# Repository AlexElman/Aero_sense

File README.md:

# Aero_sense
Can-Sat 2026/27 project group 2 from HTL Rennweg

## Core

| Component | Manufacturer / Part Number | Description |
|-----------|---------------------------|-------------|
| **MCU** | STMicroelectronics **STM32F415ZGT6** | High-performance ARM Cortex-M4 microcontroller (168 MHz, 1 MB Flash, 192 KB RAM). Selected for processing power, multiple peripherals (SPI, I²C, UART), and suitability for real-time sensor fusion and telemetry. |

## Sensors

| Component | Manufacturer / Part Number | Description |
|-----------|---------------------------|-------------|
| **Barometer** | Bosch **BMP581** | High-accuracy, low-noise absolute pressure sensor. Excellent for precise altitude determination. Digital SPI/I²C interface. Preferred over BMP390 for better noise performance and resolution. |
| **IMU** | TDK InvenSense **ICM-42688-P** | High-performance 6-axis IMU (3-axis gyroscope + 3-axis accelerometer). Low noise, high stability, SPI interface. Chosen for accurate attitude and motion sensing during flight. |
| **GNSS** | u-blox **SAM-M10Q** | Compact concurrent multi-GNSS module (GPS, GLONASS, Galileo, BeiDou). Good sensitivity and update rate for position/velocity tracking. UART interface. |
| **Temperature & Humidity** | Sensirion **SHT45** | High-accuracy digital temperature and relative humidity sensor. Excellent long-term stability and low power consumption. I²C interface. |
| **VOC / Air Quality** | Sensirion **SGP41** | Digital VOC + NOx sensor providing VOC Index and NOx Index outputs. Significantly better long-term stability and lower power than BME688. I²C interface. |

## Communication

| Component | Manufacturer / Part Number | Description |
|-----------|---------------------------|-------------|
| **LoRa Telemetry** | MicoAir **LR868F** (with 2 dBi antenna) | 868 MHz LoRa telemetry radio (500 mW). Long-range, interference-resistant link for real-time data downlink. UART interface. Suitable for CanSat telemetry ranges. |

## Power

| Component | Manufacturer / Part Number | Description |
|-----------|---------------------------|-------------|
| **Battery** | Molicel **INR-21700-P50B** (P50B) | Single high-power 21700 Li-ion cell (nominal 3.6 V, 5000 mAh, up to 60 A continuous). Excellent energy and power density for the limited volume of a CanSat. |
| **Battery Charger / PMIC** | Texas Instruments **BQ25895** | Highly integrated battery charge management IC with system power path management. Supports fast charging of the P50B cell and provides regulated system power. |

## Board-to-Board Interconnect

| Component | Manufacturer / Part Number | Description |
|-----------|---------------------------|-------------|
| **Mezzanine Connectors** | Amphenol **BergStak 0.40 mm** (2×) | Two board-to-board stacking connectors (recommended 20-pin version with 4.0 mm stack height). Provides power, SPI, I²C, UART and multiple GND connections between the three circular PCBs while offering good mechanical rigidity and vibration resistance. |

## Mechanical / PCB Notes

- Three custom semi-circular PCBs ( ≈58 mm diameter)
- Sensors requiring fresh air (BMP581, SHT45, SGP41) placed on the bottom board with controlled side vents
- Charging and data-transfer via USB-C

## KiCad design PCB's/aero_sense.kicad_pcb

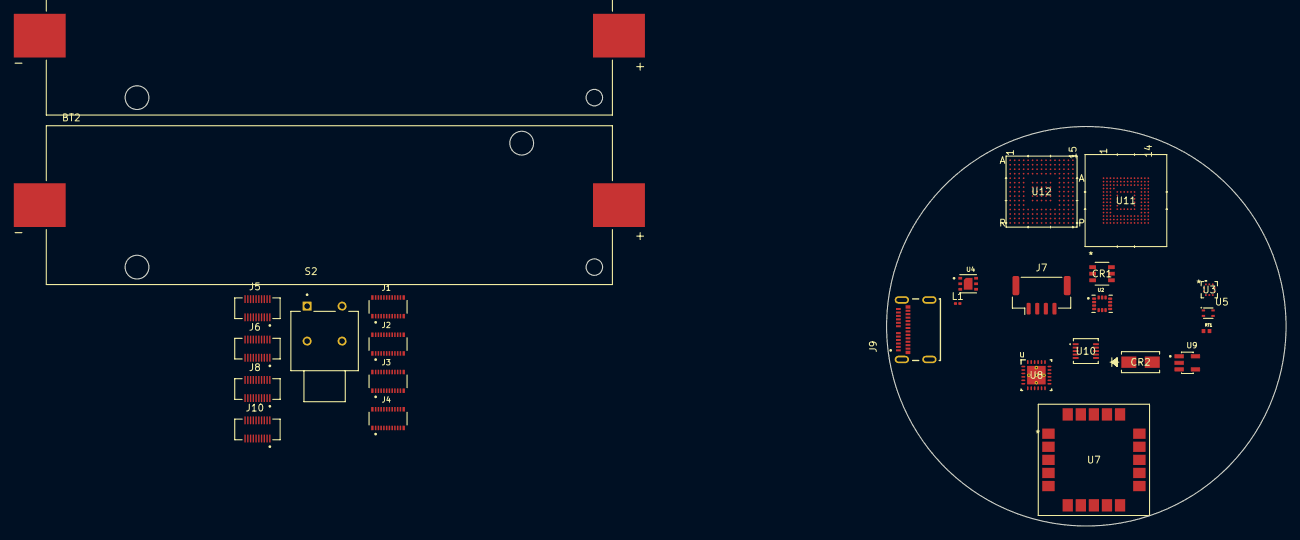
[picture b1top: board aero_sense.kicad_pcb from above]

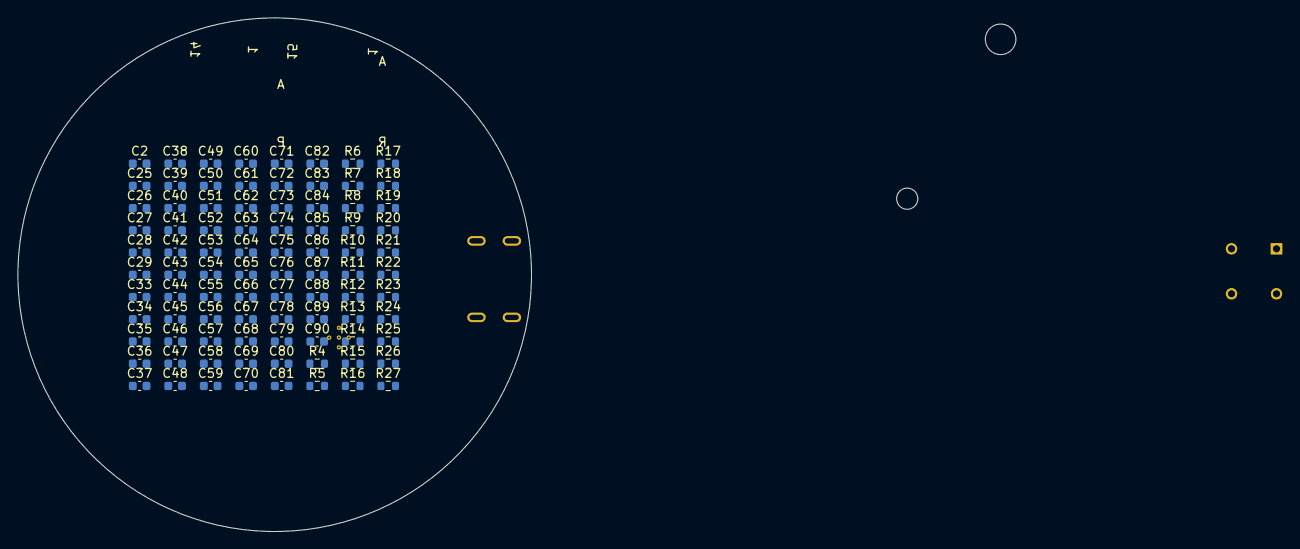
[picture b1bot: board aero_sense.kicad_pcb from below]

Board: 2 copper layers, 58.0 x 58.0 mm, 115 parts (88 on the bottom side), 50 nets, no tracks yet.

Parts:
BT1, BT2: 1122; BAT_1122
C2: 100Nf; C_0603_1608Metric
C25, C26, C27, C34, C35, C36, C37, C38, C39, C40, C41, C43, C44, C45, C46, C47, C48, C49, C50, C51, C52, C53, C54, C55, C57, C59, C73, C74, C75, C76, C77, C78, C79, C80, C82, C84, C85, C87, C88: 100nF; C_0603_1608Metric
C28, C29, C33, C42, C61, C72: 1uF; C_0603_1608Metric
C56, C58, C65, C81: 4.7uF; C_0603_1608Metric
C60, C63, C64, C67, C68, C69, C70, C71: 10uF; C_0603_1608Metric
C62: 47nF; C_0603_1608Metric
C66: 40uF; C_0603_1608Metric
C83: 2.2uF; C_0603_1608Metric
C86: 10nF; C_0603_1608Metric
C89, C90: 2uF; C_0603_1608Metric
CR1: USBLC6-2SC6; SOT23-6L_STM
CR2: SMAJ12A; SMASeries_LTF
J1, J2, J3, J4: 10164228-0201A1RLF; AMPHENOL_10164228-0201A1RLF
J5, J6, J8, J10: 10164227-0205A1RLF; AMPHENOL_10164227-0205A1RLF
J7: Conn_01x04_Pin; JST_GH_BM04B-GHS-TBT_1x04-1MP_P1.25mm_Vertical
J9: USB4081-03-A_REV0.1; GCT_USB4081-03-A_REV0.1
L1: 2uH; L_0201_0603Metric
R4, R7, R8, R11, R12, R13, R15, R16, R17, R21, R24, R25: 10kR; R_0603_1608Metric
R5: 10R; R_0603_1608Metric
R6: 10; R_0603_1608Metric
R9: 4.7R; R_0603_1608Metric
R10, R26: 0R; R_0603_1608Metric
R14: 260R; R_0603_1608Metric
R18: 3.3kR; R_0603_1608Metric
R19, R20: 5.1kR; R_0603_1608Metric
R22, R23: 22R; R_0603_1608Metric
R27: R; R_0603_1608Metric
RT1: NCP15XH103F03RC; THRMC1005X55N
S2: AB11AH-HC; SW_AB11AH-HC
U2: ICM-42688-P; PQFN50P300X250X97-14N
U3: BMP581; QFN10_BMP581_BOS
U4: SGP41-D-R4; XDCR_SGP41-D-R4
U5: SHT45-AD1F-R2; SHT4X
U7: SAM-M10Q-00B; SAM-M10Q_UBL
U8: BQ25895RTWR; RTW0024H
U9: AP2112K-3.3TRG1; SOT95P285X140-5N
U10: TS3USB221DRCR; DRC10_2P4X1P65
U11: KLM8G1GETF-B041; KLMBG2JENB-B041_SAM
U12: STM32F417IGH6; BGA 176

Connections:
42688_INT1: U2.4 (INT1/INT), U12.P2 (PA2)
Bat+: U8.13 (BAT), U8.14 (BAT)
CC1: J9.A5 (CC1), R19.1
CC2: J9.B5 (CC2), R20.1
D+BAT: U8.2 (D+), U10.1 (1D+)
D+MCU: U10.3 (2D+), U12.B15 (PA12)
D+OUT: CR1.1, J9.A6 (DP1), J9.B6 (DP2)
D-BAT: U8.3 (D-), U10.2 (1D-)
D-MCU: U10.4 (2D-), U12.C15 (PA11)
D-OUT: CR1.3, J9.A7 (DN1), J9.B7 (DN2)
DSEL: R17.2, U8.24 (DSEL), U10.9 (S)
GND: C2.2, C25.2, C26.2, C27.2, C28.2, C29.2, C33.2, C34.2, C35.2, C36.2, C37.2, C38.2, C39.2, C40.2, C41.2, C42.2, C43.2, C44.2, C45.2, C46.2, C47.2, C48.2, C49.2, C50.2, C51.2, C52.2, C53.2, C54.2, C55.2, C56.2, C57.2, C58.2, C59.2, C60.2, C61.1, C63.2, C64.2, C65.1, C66.2, C67.2, C68.2, C69.2, C70.2, C71.2, C72.2, C73.2, C81.2, C82.2, C83.2, C84.2, C85.2, C86.2, C87.2, C88.2, C89.2, C90.2, CR1.2, CR2.2, J2.1, J2.2, J2.3, J2.4, J2.17, J2.18, J2.19, J2.20, J3.1, J3.2, J3.4, J3.6, J3.8, J3.14, J3.16, J3.18, J3.19, J3.20, J5.1, J5.2, J5.4, J5.6, J5.8, J5.14, J5.16, J5.18, J5.19, J5.20, J6.1, J6.2, J6.3, J6.4, J6.17, J6.18, J6.19, J6.20, J7.1, J9.A1 (GND_A), J9.A12 (GND_A__1), J9.B1 (GND_B), J9.B12 (GND_B__1), J9.S1 (SHIELD), J9.S2 (SHIELD__1), J9.S3 (SHIELD__2), J9.S4 (SHIELD__3), J9.S5 (SHIELD__4), J9.S6 (SHIELD__5), R4.1, R14.2, R15.2, R19.2, R20.2, RT1.2, U2.2 (RESV_2), U2.3 (RESV_3), U2.6 (GND), U2.7 (RESV_7), U2.9 (INT2/FSYNC/CLKIN), U2.10 (RESV_10), U2.11 (RESV_11), U3.3 (VSS), U3.5 (SDO), U3.8 (VSS), U3.9 (VSS), U4.2 (VSS), U4.4 (N/A), U4.7 (EXP), U5.4 (VSS), U7.1 (GND), U7.4 (GND), U7.5 (GND), U7.6 (GND), U7.10 (GND), U7.11 (GND), U7.15 (GND), U7.16 (GND), U7.20 (GND), U8.9 (CE_N), U8.25 (PAD), U9.2 (GND), U10.5 (GND), U10.6 (*OE), U11.A6 (VSS), U11.C4 (VSS), U11.E7 (VSS), U11.G5 (VSS), U11.H10 (VSS), U11.J5 (VSS), U11.K8 (VSS), U11.N2 (VSS), U11.N5 (VSS), U11.P4 (VSS), U11.P6 (VSS), U12.D5 (VSS), U12.D7 (VSS), U12.D8 (VSS), U12.D9 (VSS), U12.F2 (VSS), U12.F6 (VSS), U12.F7 (VSS), U12.F8 (VSS), U12.F9 (VSS), U12.F10 (VSS), U12.F12 (VSS), U12.G2 (VSS), U12.G6 (VSS), U12.G7 (VSS), U12.G8 (VSS), U12.G9 (VSS), U12.G10 (VSS), U12.G12 (VSS), U12.H6 (VSS), U12.H7 (VSS), U12.H8 (VSS), U12.H9 (VSS), U12.H10 (VSS), U12.H12 (VSS), U12.J6 (VSS), U12.J7 (VSS), U12.J8 (VSS), U12.J9 (VSS), U12.J10 (VSS), U12.K6 (VSS), U12.K7 (VSS), U12.K8 (VSS), U12.K9 (VSS), U12.K10 (VSS), U12.M1 (VSSA), U12.M8 (VSS), U12.M9 (VSS)
I2C1_SCL: J3.12, J5.12, R7.2, U3.2 (SCK), U4.6 (SCL), U5.2 (SCL), U8.5 (SCL), U12.B6
I2C1_SDA: J3.10, J5.10, R8.2, U3.4 (SDI), U4.3 (SDA), U5.1 (SDA), U8.6 (SDA), U12.B5 (PB7)
NRST: S2.3, U12.J1 (NRST)
unnamed: C2.1, R27.1, S2.1
unnamed: C62.2, L1.1, U8.19 (SW), U8.20 (SW)
unnamed: C74.2, C75.2, C76.2, C77.2, C78.2, C79.2, C80.2
unnamed: CR1.4, R23.1
unnamed: CR1.6, R22.1
unnamed: C26.1, R6.2, U3.10 (VDD)
unnamed: C25.1, R5.2, U3.1 (VDDIO)
unnamed: C28.1, R9.2, U4.1 (VDD)
unnamed: C62.1, U8.21 (BTST)
unnamed: R14.1, U8.10 (ILIM)
unnamed: R16.1, U8.7 (INT)
unnamed: R15.1, U8.8 (OTG)
unnamed: C66.1, U8.23 (PMID)
unnamed: R21.2, RT1.1, U8.11 (TS)
unnamed: C72.1, U11.C2 (VDDI)
unnamed: R4.2, U12.D6 (BOOT0)
unnamed: R26.1, U12.C6 (PDR_ON)
REGN: C65.2, R21.1, U8.22 (REGN)
SDIO_CK: U11.M6 (CLK), U12.A12 (PC12)
SDIO_CMD: R25.1, U11.M5 (CMD), U12.D12 (PD2)
SDIO_D0: R11.1, U11.A3 (DAT0), U12.G14 (PC8)
SDIO_D1: R12.1, U11.A4 (DAT1), U12.F14 (PC9)
SDIO_D2: R13.1, U11.A5 (DAT2), U12.B14 (PC10)
SDIO_D3: R24.1, U11.B2 (DAT3), U12.B13 (PC11)
SPI1_MISO: U2.1 (AP_SDO/AP_AD0), U12.P3 (PA6)
SPI1_MOSI: U2.14 (AP_SDA/AP_SDIO/AP_SDI), U12.R3 (PA7)
SPI1_NSS: U2.12 (AP_CS), U12.N4 (PA4)
SPI1_SCK: U2.13 (AP_SCL/AP_SCLK), U12.P4 (PA5)
SYS: C63.1, C64.1, C68.1, L1.2, U8.15 (SYS), U8.16 (SYS), U9.1 (VIN), U9.3 (EN)
VBAT: C27.1, C29.1, C33.1, C34.1, C35.1, C36.1, C37.1, C38.1, C39.1, C40.1, C41.1, C42.1, C43.1, C44.1, C45.1, C46.1, C47.1, C48.1, C49.1, C50.1, C51.1, C52.1, C53.1, C54.1, C55.1, C56.1, C57.1, C58.1, C59.1, C67.1, C74.1, C75.1, C76.1, C77.1, C78.1, C79.1, C80.1, C81.1, C82.1, C83.1, C84.1, C85.1, C86.1, C87.1, C88.1, J2.5, J2.6, J2.7, J2.8, J2.9, J2.10, J2.11, J2.12, J2.13, J2.14, J2.15, J2.16, J3.3, J3.5, J3.7, J3.9, J3.11, J3.13, J3.15, J3.17, J5.3, J5.5, J5.7, J5.9, J5.11, J5.13, J5.15, J5.17, J6.5, J6.6, J6.7, J6.8, J6.9, J6.10, J6.11, J6.12, J6.13, J6.14, J6.15, J6.16, R5.1, R6.1, R7.1, R8.1, R9.1, R10.1, R11.2, R12.2, R13.2, R16.2, R17.1, R18.2, R24.2, R25.2, R27.2, U2.5 (VDDIO), U2.8 (VDD), U3.6 (CSB), U4.5 (VDDH), U5.3 (VDD), U7.2 (V_IO), U7.17 (VCC), U9.5 (VOUT), U10.10 (VCC), U11.C6 (VCCQ), U11.E6 (VCC), U11.F5 (VCC), U11.J10 (VCC), U11.K9 (VCC), U11.M4 (VCCQ), U11.N4 (VCCQ), U11.P3 (VCCQ), U11.P5 (VCCQ), U12.C1 (VBAT), U12.C5 (VDD), U12.C7 (VDD), U12.C8 (VDD), U12.C9 (VDD), U12.F3 (VDD), U12.G3 (VDD), U12.G13 (VDD), U12.H13 (VDD), U12.J12 (VDD), U12.J13 (VDD), U12.K4 (VDD), U12.N8 (VDD), U12.N9 (VDD), U12.N10 (VDD), U12.R1 (VDDA)
VBUS: C60.1, C61.2, C69.1, C70.1, C71.1, C73.1, CR1.5, CR2.1, J9.A4 (VBUS_A), J9.A9 (VBUS_A__1), J9.B4 (VBUS_B), J9.B9 (VBUS_B__1), U8.1 (VBUS)
VCAP_1: C89.1, U12.M10 (VCAP_1)
VCAP_2: C90.1, U12.F13 (VCAP_2)
VREF+: R10.2, U12.P1 (VREF+)
eMMC RSTN: U11.K5 (RSTN), U12.N2 (PA1)
